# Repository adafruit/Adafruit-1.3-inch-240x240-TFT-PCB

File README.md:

## Adafruit 1.3" 240x240 Wide Angle TFT LCD Display with MicroSD PCB

<a href="http://www.adafruit.com/products/4313"><br/>
Click here to purchase one from the Adafruit shop</a>

PCB files for the Adafruit 1.3" 240x240 Wide Angle TFT LCD Display with MicroSD. 

Format is EagleCAD schematic and board layout
* https://www.adafruit.com/product/4313

### Description

We've been looking for a display like this for a long time - it's so small only 1.3" diagonal but has a high density 260 ppi, 240x240 pixel display with full-angle viewing. It looks a lot like our 1.44" 128x128 display, but has 4x as many pixels and looks great at any angle. We've seen displays of this caliber used in smartwatches and small electronic devices but they've always been MIPI interface. Finally, we found one that is SPI and has a friendly display driver, so it works with any and all microcontrollers or microcomputers!

This lovely little display breakout is the best way to add a small, colorful and very bright display to any project. Since the display uses 4-wire SPI to communicate and has its own pixel-addressable frame buffer, it can be used with every kind of microcontroller. Even a very small one with low memory and few pins available! The 1.3" display has 240x240 16-bit full color pixels and is an IPS display, so the color looks great up to 80 degrees off axis in any direction. The TFT driver (ST7789) is very similar to the popular ST7735, and our Arduino library supports it well.

Our breakout has the TFT display soldered on (it uses a delicate flex-circuit connector) as well as a ultra-low-dropout 3.3V regulator and a 3/5V level shifter so you can use it with 3.3V or 5V power and logic. We also had a little space so we placed a microSD card holder so you can easily load full color bitmaps from a FAT16/FAT32 formatted microSD card. The microSD card is not included, but you can pick one up here.

Of course, we wouldn't just leave you with a datasheet and a "good luck!" - we've written a full open source graphics library that can draw pixels, lines, rectangles, circles, text and bitmaps as well as example code and a wiring tutorial. The code is written for Arduino but can be easily ported to your favorite microcontroller!

### License

Adafruit invests time and resources providing this open source design, please support Adafruit and open-source hardware by purchasing products from [Adafruit](https://www.adafruit.com)!

Designed by Limor Fried/Ladyada for Adafruit Industries.

Creative Commons Attribution/Share-Alike, all text above must be included in any redistribution. 
See license.txt for additional details.

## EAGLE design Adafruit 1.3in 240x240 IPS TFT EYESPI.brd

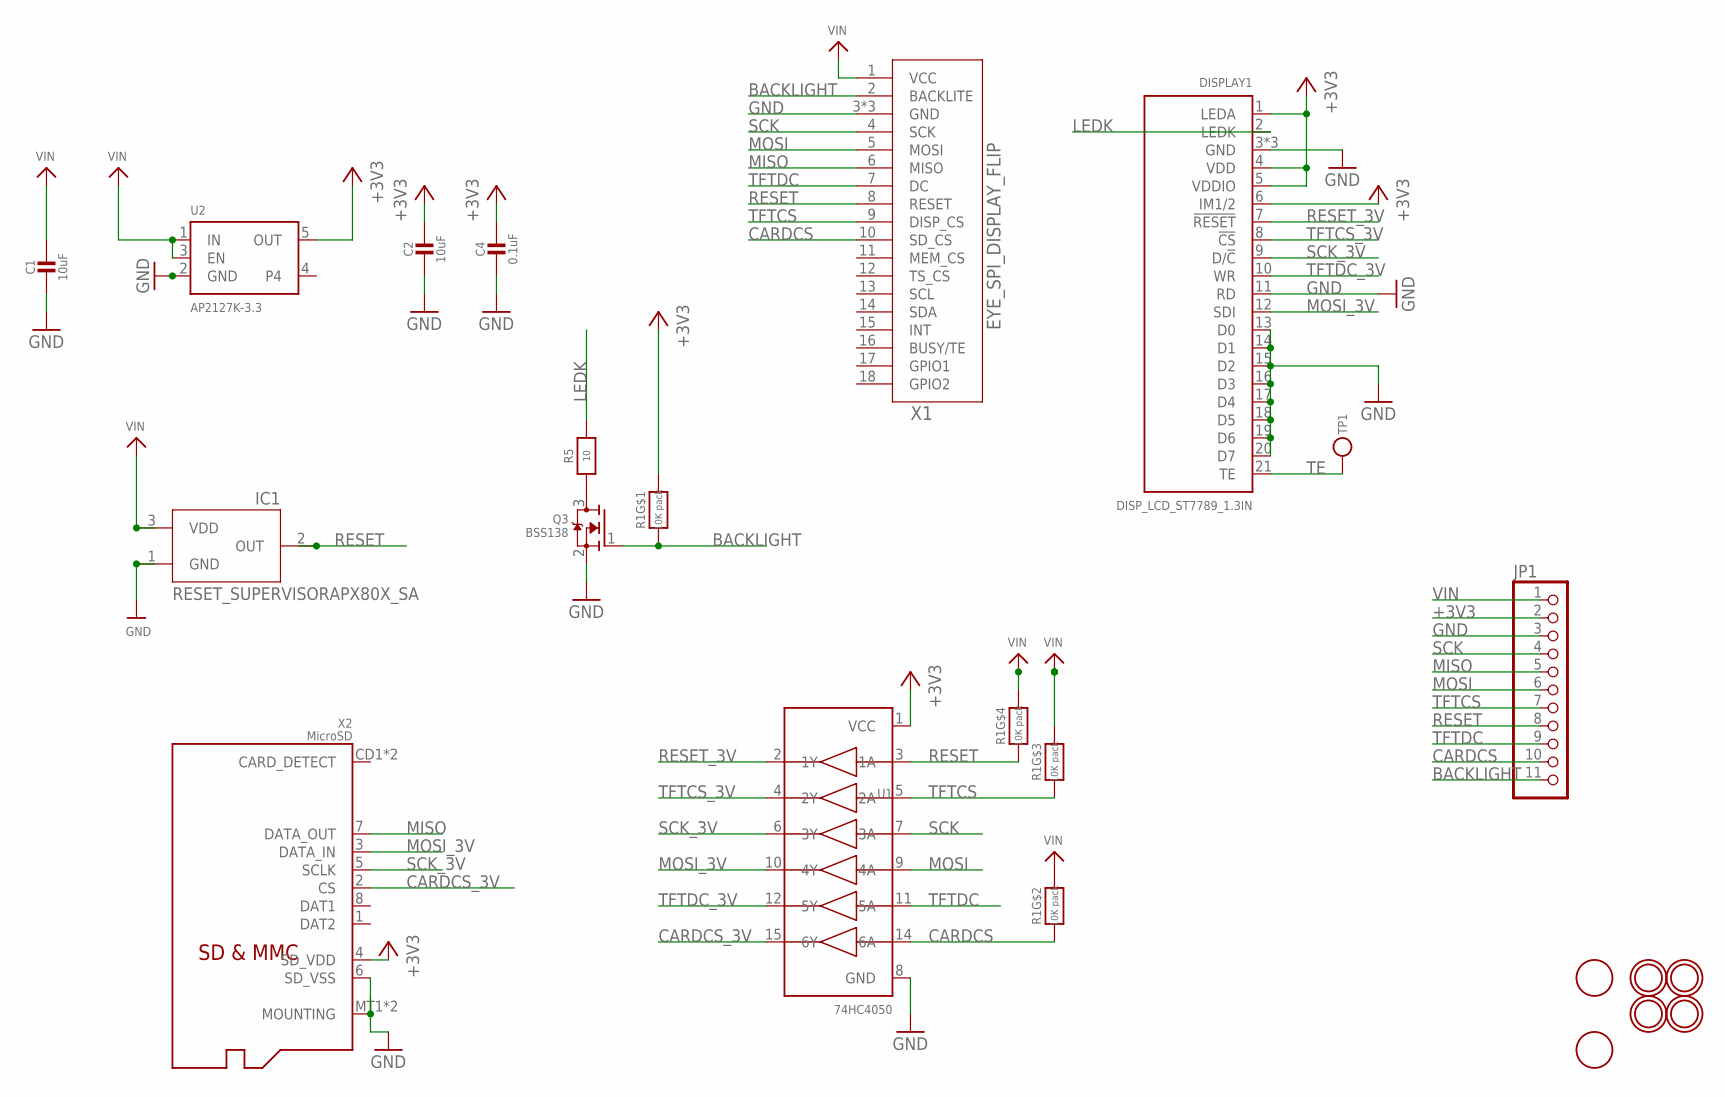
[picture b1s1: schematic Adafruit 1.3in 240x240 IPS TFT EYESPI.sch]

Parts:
C1, C2: 10uF; 0805-NO
C4: 0.1uF; 0603-NO
DISPLAY1: DISP_LCD_ST7789_1.3IN; TFT_1.3IN_240X240_24P
IC1: RESET_SUPERVISORAPX80X_SA; SOT23-WIDE
JP1: HEADER-1X1176MIL; 1X11_ROUND_76
Q3: BSS138; SOT23-WIDE
R1: 10K pack; RESPACK_4X0603
R5: 10; 0603-NO
TP1: TESTPOINTROUND1.5MM; TESTPOINT_ROUND_1.5MM
U1: 74HC4050; TSSOP16
U2: AP2127K-3.3; SOT23-5
U$4, U$5: FIDUCIAL; FIDUCIAL_1MM
U$7, U$8, U$9, U$10: MOUNTINGHOLE2.5; MOUNTINGHOLE_2.5_PLATED
X1: EYE_SPI_DISPLAY_FLIP; EYE_SPI_DISPLAY_BOTCONTACT
X2: MicroSD; MICROSD

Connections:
+3V3: C2.1, C4.1, DISPLAY1.1 (LEDA), DISPLAY1.4 (VDD), DISPLAY1.5 (VDDIO), DISPLAY1.6 (IM1/2), JP1.2, R1.8 (2), U1.1 (VCC), U2.5 (OUT), X2.4 (SD_VDD)
BACKLIGHT: JP1.11, Q3.1 (G), R1.1, X1.2 (BACKLITE)
CARDCS: JP1.10, R1.2 (1), U1.14 (6A), X1.10 (SD_CS)
CARDCS_3V: U1.15 (6Y), X2.2 (CS)
GND: C1.2, C2.2, C4.2, DISPLAY1.3 (GND), DISPLAY1.11 (RD), DISPLAY1.13 (D0), DISPLAY1.14 (D1), DISPLAY1.15 (D2), DISPLAY1.16 (D3), DISPLAY1.17 (D4), DISPLAY1.18 (D5), DISPLAY1.19 (D6), DISPLAY1.20 (D7), DISPLAY1.23 (GND), DISPLAY1.24 (GND), IC1.1 (GND), JP1.3, Q3.2 (S), U1.8 (GND), U2.2 (GND), X1.3 (GND), X1.SUPPORT1 (GND), X1.SUPPORT2 (GND), X2.6 (SD_VSS), X2.MT1 (MOUNTING), X2.MT2 (MOUNTING)
LEDK: DISPLAY1.2 (LEDK), R5.2
MISO: JP1.5, X1.6 (MISO), X2.7 (DATA_OUT)
MOSI: JP1.6, U1.9 (4A), X1.5 (MOSI)
MOSI_3V: DISPLAY1.12 (SDI), U1.10 (4Y), X2.3 (DATA_IN)
unnamed: Q3.3 (D), R5.1
RESET: IC1.2 (OUT), JP1.8, R1.4 (1), U1.3 (1A), X1.8 (RESET)
RESET_3V: DISPLAY1.7 (!RESET), U1.2 (1Y)
SCK: JP1.4, U1.7 (3A), X1.4 (SCK)
SCK_3V: DISPLAY1.9 (D/!C), U1.6 (3Y), X2.5 (SCLK)
TE: DISPLAY1.21 (TE), TP1.P$1
TFTCS: JP1.7, R1.3 (1), U1.5 (2A), X1.9 (DISP_CS)
TFTCS_3V: DISPLAY1.8 (!CS), U1.4 (2Y)
TFTDC: JP1.9, U1.11 (5A), X1.7 (DC)
TFTDC_3V: DISPLAY1.10 (WR), U1.12 (5Y)
VIN: C1.1, IC1.3 (VDD), JP1.1, R1.5 (2), R1.6 (2), R1.7 (2), U2.1 (IN), U2.3 (EN), X1.1 (VCC)

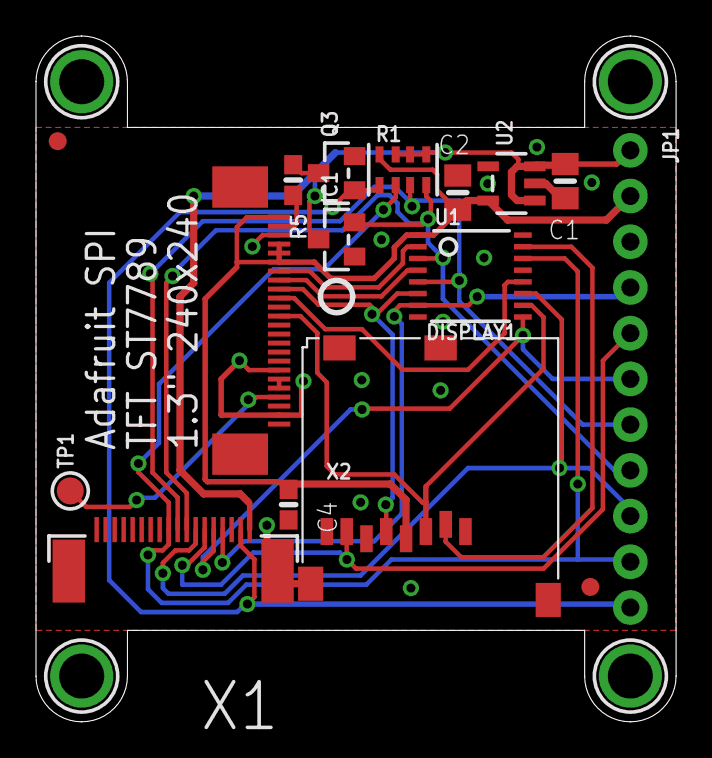
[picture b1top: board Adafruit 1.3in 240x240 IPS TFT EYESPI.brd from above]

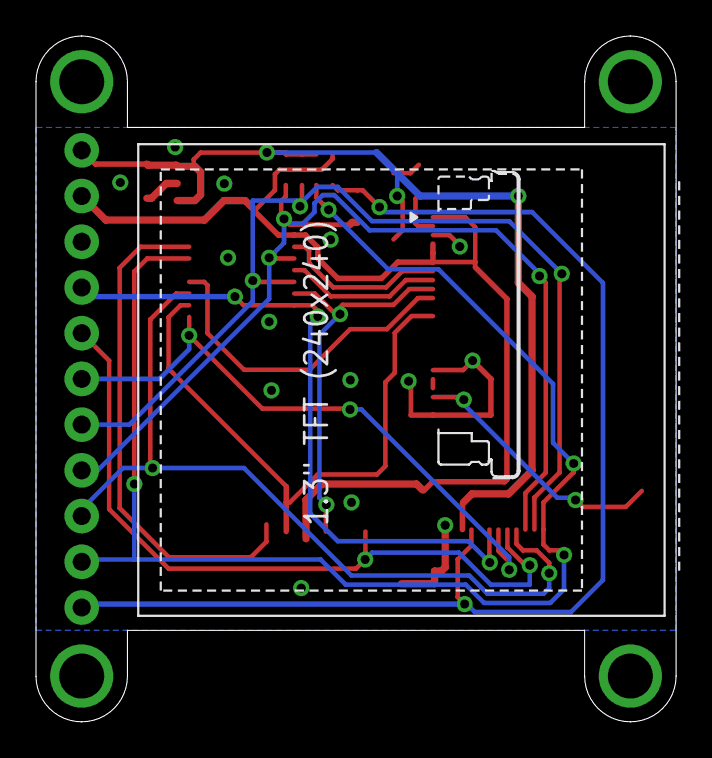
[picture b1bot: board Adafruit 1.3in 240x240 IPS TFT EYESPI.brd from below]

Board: 2 copper layers, 35.6 x 38.1 mm, 45 parts (11 on the bottom side), 20 nets.

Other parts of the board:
PLABEL0: PLABEL0
PLABEL1: PLABEL1
PLABEL2: PLABEL2
PLABEL3: PLABEL3
PLABEL4: PLABEL4
PLABEL5: PLABEL5
PLABEL6: PLABEL6
PLABEL7: PLABEL7
PLABEL8: PLABEL8
PLABEL9: PLABEL9
PLABEL10: PLABEL10
PLABEL11: PLABEL11
PLABEL13: PLABEL13
PLABEL14: PLABEL14
PLABEL15: PLABEL15
PLABEL16: PLABEL16
PLABEL17: PLABEL17
PLABEL18: PLABEL18
PLABEL19: PLABEL19
PLABEL20: PLABEL20
PLABEL21: PLABEL21
PLABEL22: PLABEL22
PLABEL23: PLABEL23
PLABEL24: PLABEL24
U$2: PCBFEAT-REV-040

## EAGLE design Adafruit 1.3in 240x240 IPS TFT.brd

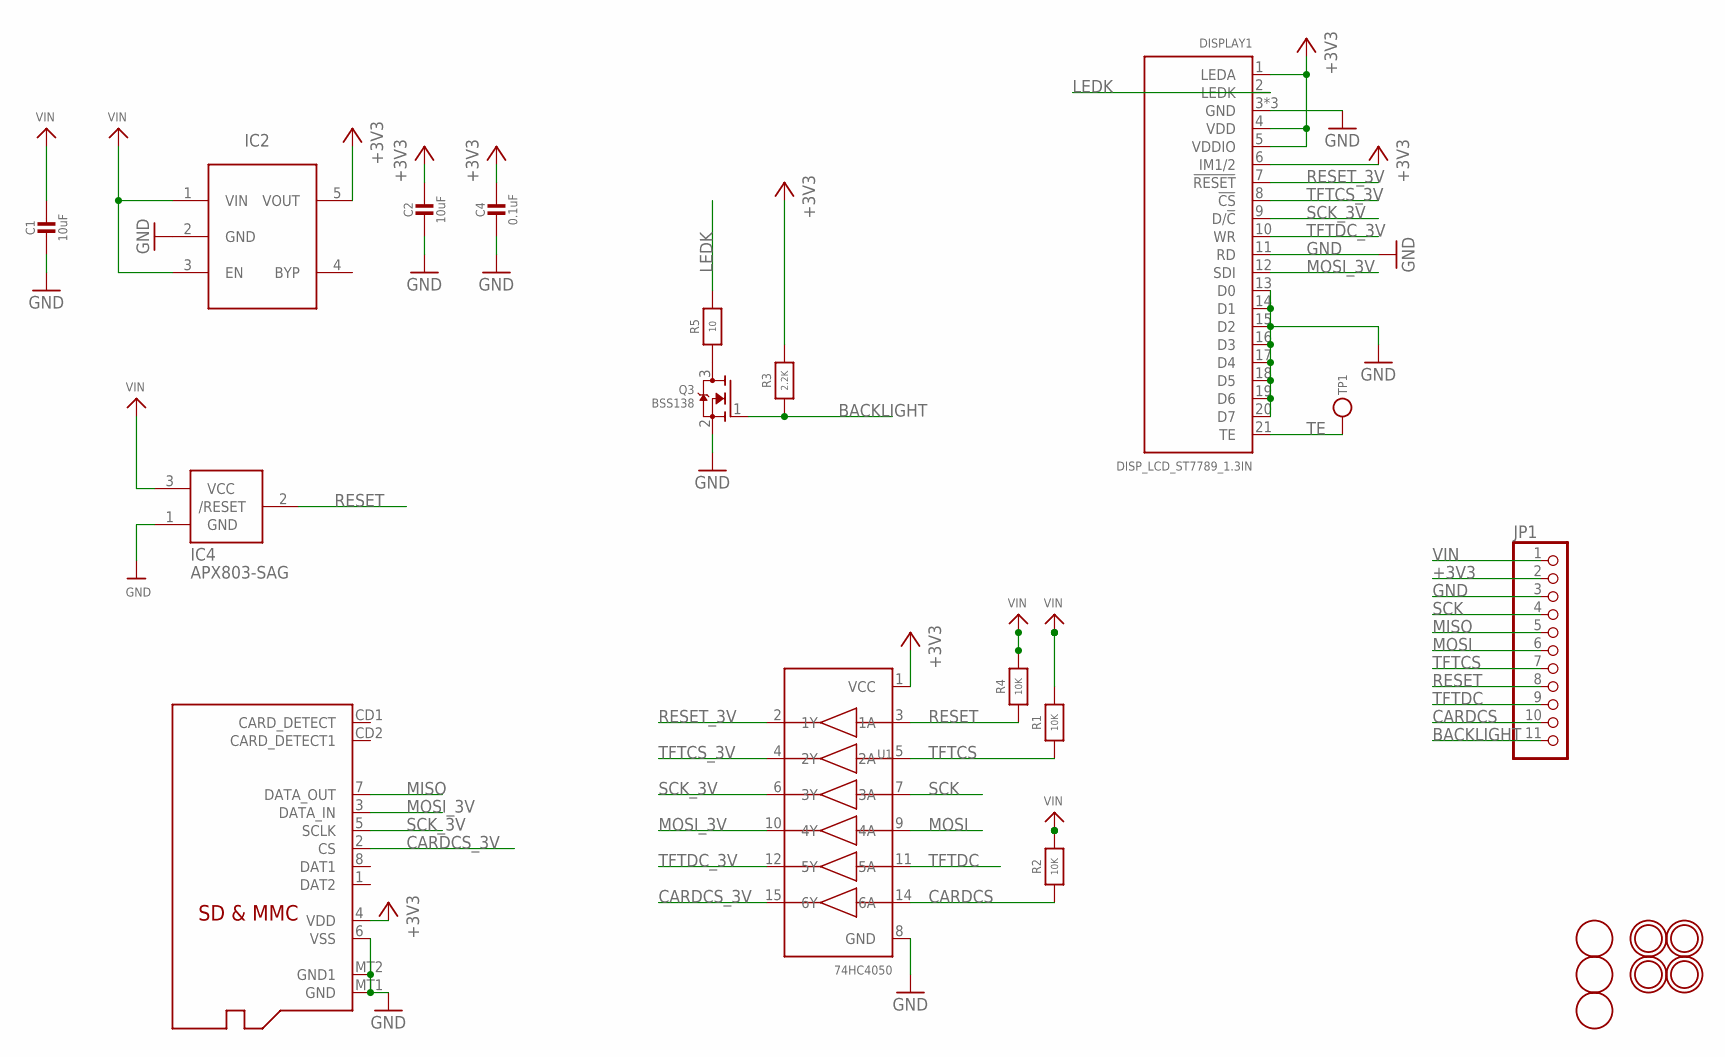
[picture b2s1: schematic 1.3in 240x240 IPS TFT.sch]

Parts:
C1, C2: 10uF; 0805-NO
C4: 0.1uF; 0603-NO
DISPLAY1: DISP_LCD_ST7789_1.3IN; TFT_1.3IN_240X240_24P
IC2: AP2112K-3.3; SOT23-5L
IC4: APX803-SAG; SOT23
JP1: HEADER-1X1176MIL; 1X11_ROUND_76
Q2: MICROSD
Q3: BSS138; SOT23-WIDE
R1, R2, R4: 10K; 0603-NO
R3: 2.2K; 0603-NO
R5: 10; 0603-NO
TP1: TESTPOINTROUND1.5MM; TESTPOINT_ROUND_1.5MM
U1: 74HC4050; TSSOP16
U$3, U$4, U$5: FIDUCIAL; FIDUCIAL_1MM
U$7, U$8, U$9, U$10: MOUNTINGHOLE2.5; MOUNTINGHOLE_2.5_PLATED

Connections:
+3V3: C2.1, C4.1, DISPLAY1.1 (LEDA), DISPLAY1.4 (VDD), DISPLAY1.5 (VDDIO), DISPLAY1.6 (IM1/2), IC2.5 (VOUT), JP1.2, Q2.4 (VDD), R3.2, U1.1 (VCC)
BACKLIGHT: JP1.11, Q3.1 (G), R3.1
CARDCS: JP1.10, R2.1, U1.14 (6A)
CARDCS_3V: Q2.2 (CS), U1.15 (6Y)
GND: C1.2, C2.2, C4.2, DISPLAY1.3 (GND), DISPLAY1.11 (RD), DISPLAY1.13 (D0), DISPLAY1.14 (D1), DISPLAY1.15 (D2), DISPLAY1.16 (D3), DISPLAY1.17 (D4), DISPLAY1.18 (D5), DISPLAY1.19 (D6), DISPLAY1.20 (D7), DISPLAY1.23 (GND), DISPLAY1.24 (GND), IC2.2 (GND), IC4.1 (GND), JP1.3, Q2.6 (VSS), Q2.MT1 (GND), Q2.MT2 (GND1), Q3.2 (S), U1.8 (GND)
LEDK: DISPLAY1.2 (LEDK), R5.2
MISO: JP1.5, Q2.7 (DATA_OUT)
MOSI: JP1.6, U1.9 (4A)
MOSI_3V: DISPLAY1.12 (SDI), Q2.3 (DATA_IN), U1.10 (4Y)
unnamed: Q3.3 (D), R5.1
RESET: IC4.2 (/RESET), JP1.8, R4.1, U1.3 (1A)
RESET_3V: DISPLAY1.7 (!RESET), U1.2 (1Y)
SCK: JP1.4, U1.7 (3A)
SCK_3V: DISPLAY1.9 (D/!C), Q2.5 (SCLK), U1.6 (3Y)
TE: DISPLAY1.21 (TE), TP1.P$1
TFTCS: JP1.7, R1.1, U1.5 (2A)
TFTCS_3V: DISPLAY1.8 (!CS), U1.4 (2Y)
TFTDC: JP1.9, U1.11 (5A)
TFTDC_3V: DISPLAY1.10 (WR), U1.12 (5Y)
VIN: C1.1, IC2.1 (VIN), IC2.3 (EN), IC4.3 (VCC), JP1.1, R1.2, R2.2, R4.2

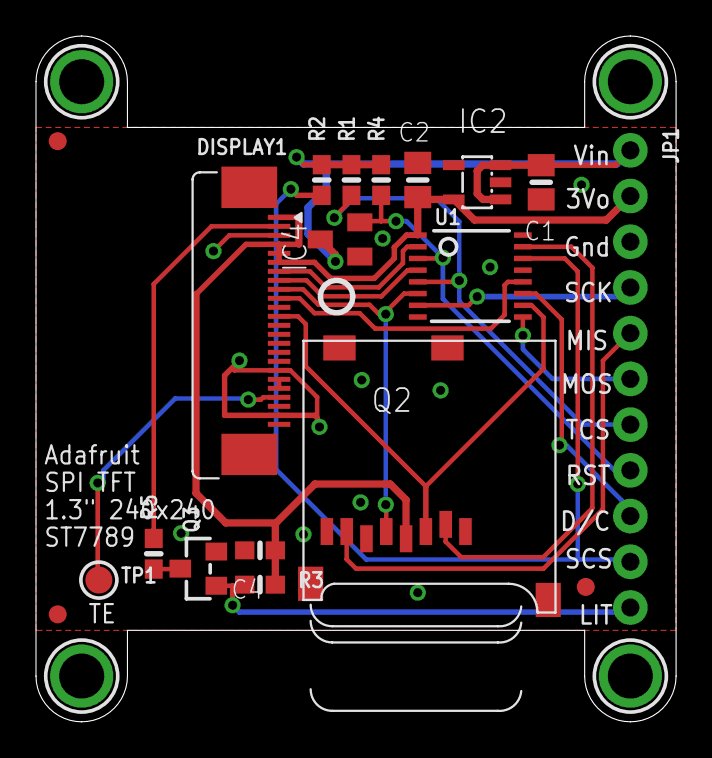
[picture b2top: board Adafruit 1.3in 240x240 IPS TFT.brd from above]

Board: 2 copper layers, 35.6 x 38.1 mm, 24 parts (0 on the bottom side), 20 nets.

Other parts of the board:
U$2: PCBFEAT-REV-040

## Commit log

2019-08-07 Adding board/repo files.
2019-08-07 Updated board file names.
2023-07-24 Add updated board files.

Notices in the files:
parts and their libraries:
microbuilder: This work is placed in the public domain, and may be freely used for commercial and non-commercial work with the following conditions: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
